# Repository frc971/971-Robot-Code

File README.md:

# **THIS REPO IS NOW ARCHIVED AND READ ONLY.**

# Introduction
This is FRC Team 971's main code repository. There are `README*` files throughout the source tree documenting specifics for their respective folders.

## Contributing
Submissions must be made under the terms of the following Developer Certificate of Origin.

By making a contribution to this project, I certify that:

        (a) The contribution was created in whole or in part by me and I
            have the right to submit it under the open source license
            indicated in the file; or

        (b) The contribution is based upon previous work that, to the best
            of my knowledge, is covered under an appropriate open source
            license and I have the right under that license to submit that
            work with modifications, whether created in whole or in part
            by me, under the same open source license (unless I am
            permitted to submit under a different license), as indicated
            in the file; or

        (c) The contribution was provided directly to me by some other
            person who certified (a), (b) or (c) and I have not modified
            it.

        (d) I understand and agree that this project and the contribution
            are public and that a record of the contribution (including all
            personal information I submit with it, including my sign-off) is
            maintained indefinitely and may be redistributed consistent with
            this project or the open source license(s) involved.

To do this, add the following to your commit message.  Gerrit will enforce that all commits have been signed off.

	Signed-off-by: Random J Developer <random@developer.example.org>

Git has support for adding Signed-off-by lines by using `git commit -s`, or you can setup a git commit hook to automatically sign off your commits.  [Stack Overflow](https://stackoverflow.com/questions/15015894/git-add-signed-off-by-line-using-format-signoff-not-working) has instructions for how to do this if you are interested.

## Table of contents
* [Pathway for new members](#pathway-for-new-members)
    * [Learning C++](#1-learning-c)
        * [XRP](#11-xrp)
    * [Gaining code access](#2-gaining-code-access)
    * [The codelab](#3-the-codelab)
* [Code Reviews](#code-reviews)
    * [Creating SSH Aliases](#creating-ssh-aliases)
* [Codelab](#codelab)
* [Other Information](#other-information)
    * [Roborio Kernel Traces](#roborio-kernel-traces)
    * [Notes on troubleshooting network setup](#notes-on-troubleshooting-network-setup)
    * [LSP Setup for Rust](#lsp-setup-for-rust)
    * [Other resources](#other-resources)

## Pathway for new members

### 1. Learning C++

C++ is what we use to program a majority of the code which runs on the robot.
We generally recommend [this course by codeacademy](https://www.codecademy.com/learn/learn-c-plus-plus) which goes over the basics of C++ as well as OOP.

#### 1.1 XRP

If you are unsure what to work on yet you can start on the [XRP Platform](https://docs.wpilib.org/en/stable/docs/xrp-robot/index.html).
Which basically lets you use smaller robots to learn about robotics through WPILib.

### 2. Gaining code access

You can follow [these steps](./documentation/tutorials/getting-started.md) to access the code.

There is also a document which goes over the basics of using both gerrit and git [here](./documentation/tutorials/git-and-gerrit-basics.md)

### 3. The codelab

Once you have an understanding of C++ and have gone through using all the steps needed to access the code you can start on the codelab, which is a directory living in `frc971/codelab/`. Which goes over a lot of the important introductory information that you need to know to get started when programming the robot.
You can read the [README](./frc971/codelab/README.md), which gives you introduces you to the codelab as well as the concepts you need to understand first.

## Code reviews
We want all code to at least have a second person look it over before it gets merged into the `main` branch. Gerrit has [extensive documentation on starting reviews](https://gerrit-review.googlesource.com/Documentation/user-upload.html).  There is also a good [intro User Guide](https://gerrit-review.googlesource.com/Documentation/intro-user.html) and an [intro to working with Gerrit](https://gerrit-review.googlesource.com/Documentation/intro-gerrit-walkthrough.html) and [Gerrit workflows](https://docs.google.com/presentation/d/1C73UgQdzZDw0gzpaEqIC6SPujZJhqamyqO1XOHjH-uk)

TL;DR: Make and commit your changes, do `git push origin HEAD:refs/for/main`, and then click on the provided link to add reviewers.  If you just upload a change without adding any reviewers, it might sit around for a long time before anybody else notices it.

[git-review](http://manpages.debian.org/cgi-bin/man.cgi?query=git-review) can make the upload process simpler.

To download a commit you can press d or click download on gerrit, then select fetch and paste the command in your terminal. Once you've done that you should switch to a new branch in order to make working on multiple commits easier.
You can do this by doing `git switch -c branch_name`, the branch name can be anything, and will only be public for you, so organize in whatever way you find easy to model.

When programming in C++ we follow [Google's C++ Style Guide](https://google.github.io/styleguide/cppguide.html)

Furthermore, you can run `bazel run //tools/lint:run-ci` to fix linter errors which appear on buildkite.

### Some other useful packages
These aren't strictly necessary to build the code, but Michael found the
additional tools provided by these packages useful to install when working with
the code on May 13, 2018.

> **Note**: These are for local install, most of these tools will be available on the build server

```bash
apt install git
apt install yapf3
apt install python3
apt install bazel
apt install clang-format
```

### Creating ssh aliases

It is also handy to alias logins to the raspberry pi's by adding lines like this to your ~/.ssh/config file:
```console
Host pi-7971-2
    User pi
    ForwardAgent yes
    HostName 10.79.71.102
    StrictHostKeyChecking no
```
or, for the roborio:
```
Host roborio-971
    User admin
    HostName 10.9.71.2
    StrictHostKeyChecking no
```
This allows you to use the alias to `ping`, `ssh`, or run commands like:
```
# Download code to robot #7971's raspberry pi #2
bazel run --config=armv7 -c opt //y2020:download_stripped -- pi-7971-2
```

## Other Information

### Roborio Kernel Traces

Currently (as of 2020.02.26), top tends to produce misleading statistics. As
such, you can get more useful information about CPU usage by using kernel
traces. Sample usage:
```console
# Note that you will need to install the trace-cmd package on the roborio.
# This may be not be a trivial task.
# Start the trace
trace-cmd start -e sched_switch -e workqueue
# Stop the trace
trace-cmd stop
# Save the trace to trace.dat
trace-cmd extract
```
You can then scp the `trace.dat` file to your computer and run `kernelshark
trace.dat` (may require installing the `kernelshark` apt package).

### LSP Setup for Rust

You can run `bazel run //tools:gen_rust_project` to generate a rust-project.json
file which rust-analyzer will pick up. You will need to execute this rule
periodically as it will be outdated whenever the BUILD files change.

> **Note** that there's currently no way to tell rust-analyzer *how* to compile
the code, so while it will give you completion support, go to definition, and
other niceties, it won't show compilation errors or warnings at this point.

### Other resources
  1. Intro to [AOS](./aos/README.md), our robot Operating System
  2. Introductory example: [ping/pong](./aos/events/README.md)
  3. Example of [logging](./aos/events/README.md)

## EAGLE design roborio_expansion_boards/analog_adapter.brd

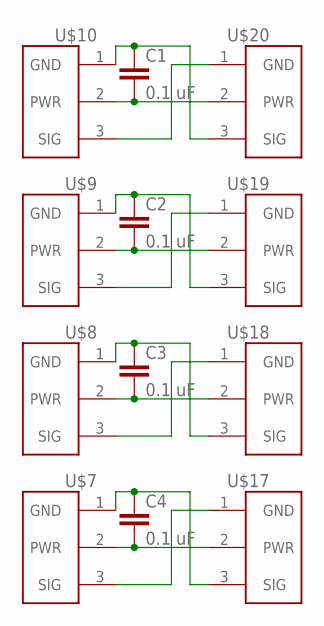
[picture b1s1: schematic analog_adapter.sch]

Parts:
C1, C2, C3, C4: 0.1 uF; 0603
U$7, U$8, U$9, U$10: 22-23-2031GENERIC; PWM_1X3
U$17, U$18, U$19, U$20: 22-23-2031

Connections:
unnamed: C1.1, U$10.1 (GND), U$20.3 (SIG)
unnamed: C1.2, U$10.2 (PWR), U$20.2 (PWR)
unnamed: U$10.3 (SIG), U$20.1 (GND)
unnamed: C2.2, U$9.2 (PWR), U$19.2 (PWR)
unnamed: U$9.3 (SIG), U$19.1 (GND)
unnamed: C3.2, U$8.2 (PWR), U$18.2 (PWR)
unnamed: U$8.3 (SIG), U$18.1 (GND)
unnamed: C4.2, U$7.2 (PWR), U$17.2 (PWR)
unnamed: U$7.3 (SIG), U$17.1 (GND)
unnamed: C4.1, U$7.1 (GND), U$17.3 (SIG)
unnamed: C3.1, U$8.1 (GND), U$18.3 (SIG)
unnamed: C2.1, U$9.1 (GND), U$19.3 (SIG)

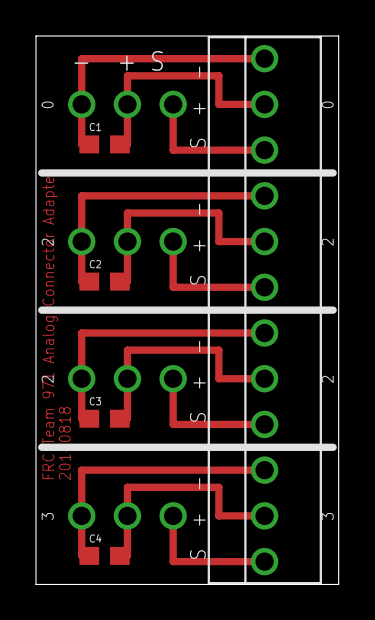
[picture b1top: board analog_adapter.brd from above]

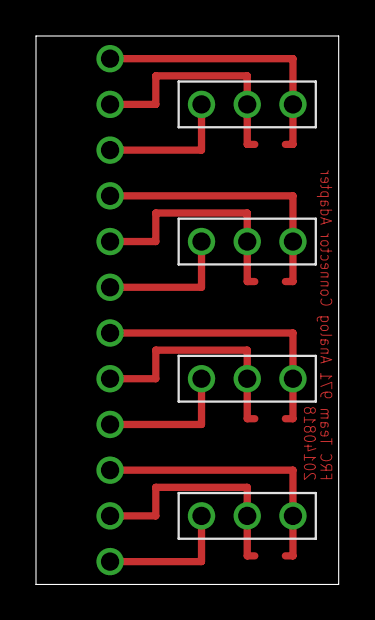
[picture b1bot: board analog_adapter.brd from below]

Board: 2 copper layers, 16.8 x 30.5 mm, 12 parts (4 on the bottom side), 12 nets.

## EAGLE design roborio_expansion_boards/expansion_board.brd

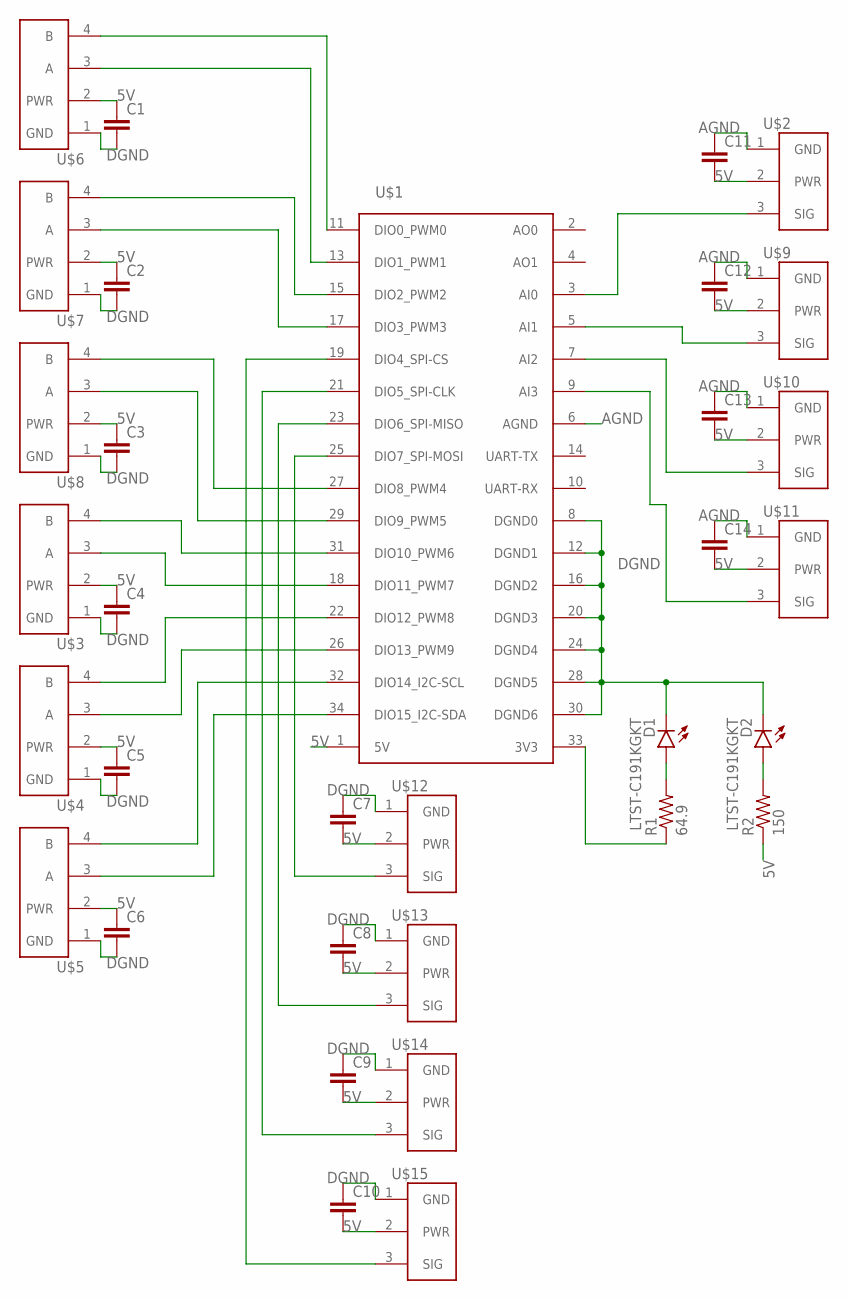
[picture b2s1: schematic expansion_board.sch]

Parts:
C1, C2, C3, C4, C5, C6, C7, C8, C9, C10, C11, C12, C13, C14: CAP0603; 0603
D1, D2: LTST-C191KGKT; LED-0603
R1: 64.9; 0603-RES
R2: 150; 0603-RES
U$1: MXP; SFH11-PBPC-D17-ST-BK
U$2, U$9, U$10, U$11, U$12, U$13, U$14, U$15: 22-23-2031
U$3, U$4, U$5, U$6, U$7, U$8: 22-23-2041

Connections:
5V: C1.1, C2.1, C3.1, C4.1, C5.1, C6.1, C7.2, C8.2, C9.2, C10.2, C11.2, C12.2, C13.2, C14.2, R2.1, U$1.1 (5V), U$2.2 (PWR), U$3.2 (PWR), U$4.2 (PWR), U$5.2 (PWR), U$6.2 (PWR), U$7.2 (PWR), U$8.2 (PWR), U$9.2 (PWR), U$10.2 (PWR), U$11.2 (PWR), U$12.2 (PWR), U$13.2 (PWR), U$14.2 (PWR), U$15.2 (PWR)
AGND: C11.1, C12.1, C13.1, C14.1, U$1.6 (AGND), U$2.1 (GND), U$9.1 (GND), U$10.1 (GND), U$11.1 (GND)
DGND: C1.2, C2.2, C3.2, C4.2, C5.2, C6.2, C7.1, C8.1, C9.1, C10.1, D1.C, D2.C, U$1.8 (DGND0), U$1.12 (DGND1), U$1.16 (DGND2), U$1.20 (DGND3), U$1.24 (DGND4), U$1.28 (DGND5), U$1.30 (DGND6), U$3.1 (GND), U$4.1 (GND), U$5.1 (GND), U$6.1 (GND), U$7.1 (GND), U$8.1 (GND), U$12.1 (GND), U$13.1 (GND), U$14.1 (GND), U$15.1 (GND)
unnamed: U$1.11 (DIO0_PWM0), U$6.4 (B)
unnamed: U$1.13 (DIO1_PWM1), U$6.3 (A)
unnamed: U$1.15 (DIO2_PWM2), U$7.4 (B)
unnamed: U$1.17 (DIO3_PWM3), U$7.3 (A)
unnamed: U$1.27 (DIO8_PWM4), U$8.4 (B)
unnamed: U$1.29 (DIO9_PWM5), U$8.3 (A)
unnamed: U$1.31 (DIO10_PWM6), U$3.4 (B)
unnamed: U$1.18 (DIO11_PWM7), U$3.3 (A)
unnamed: U$1.22 (DIO12_PWM8), U$4.4 (B)
unnamed: U$1.26 (DIO13_PWM9), U$4.3 (A)
unnamed: U$1.32 (DIO14_I2C-SCL), U$5.4 (B)
unnamed: U$1.34 (DIO15_I2C-SDA), U$5.3 (A)
unnamed: U$1.3 (AI0), U$2.3 (SIG)
unnamed: U$1.5 (AI1), U$9.3 (SIG)
unnamed: U$1.7 (AI2), U$10.3 (SIG)
unnamed: U$1.9 (AI3), U$11.3 (SIG)
unnamed: U$1.25 (DIO7_SPI-MOSI), U$12.3 (SIG)
unnamed: U$1.23 (DIO6_SPI-MISO), U$13.3 (SIG)
unnamed: U$1.21 (DIO5_SPI-CLK), U$14.3 (SIG)
unnamed: U$1.19 (DIO4_SPI-CS), U$15.3 (SIG)
unnamed: D1.A, R1.2
unnamed: R1.1, U$1.33 (3V3)
unnamed: D2.A, R2.2

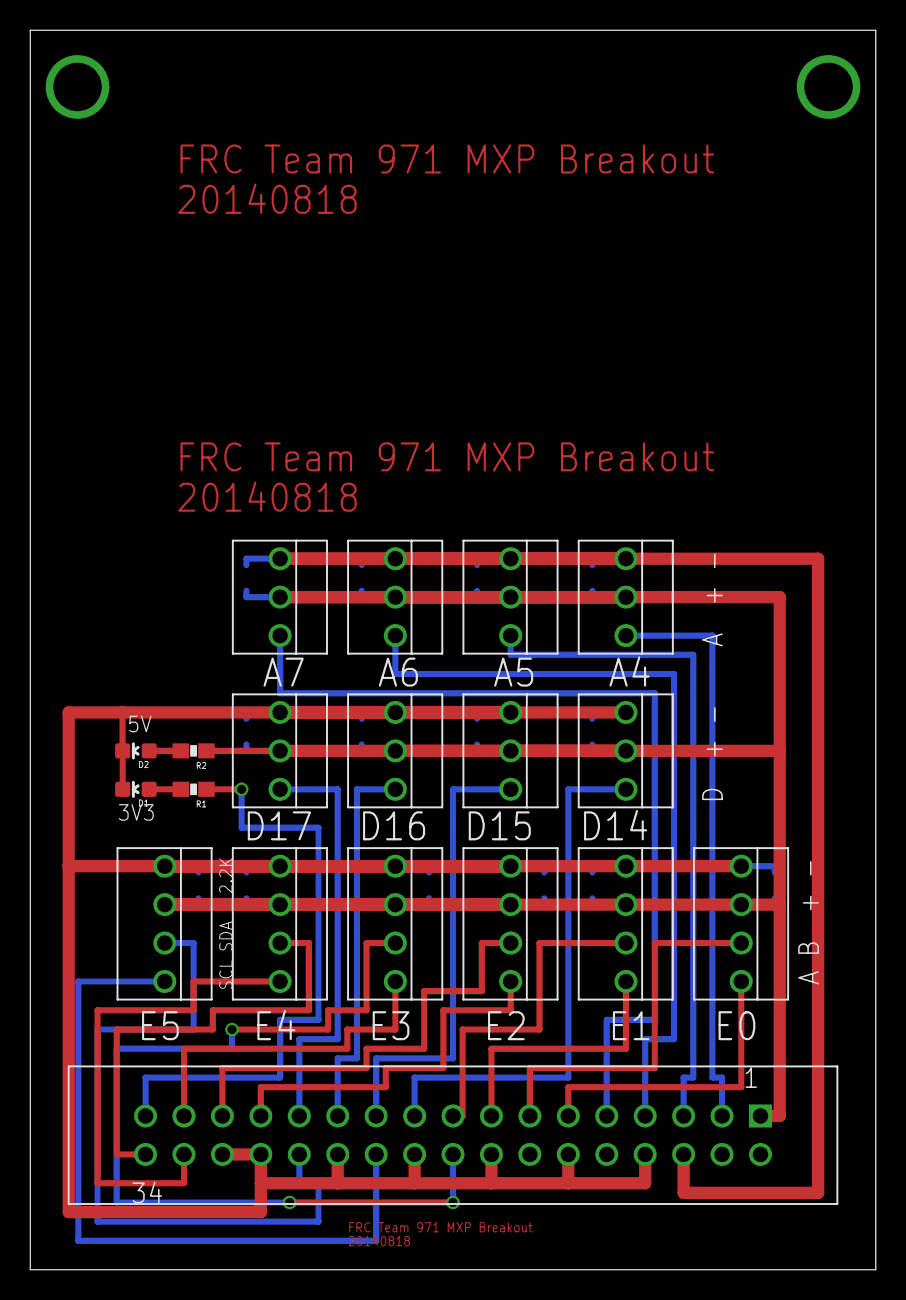
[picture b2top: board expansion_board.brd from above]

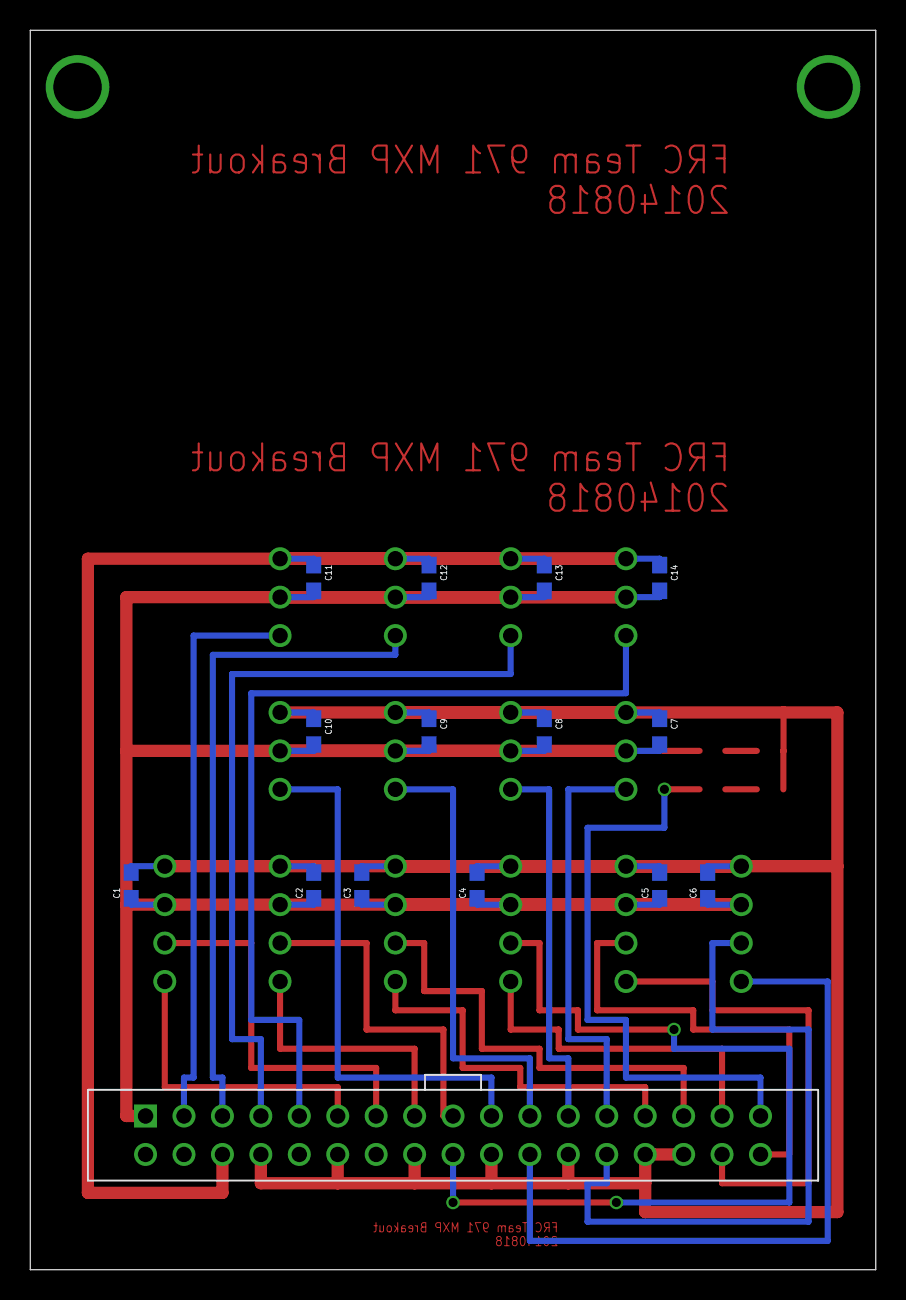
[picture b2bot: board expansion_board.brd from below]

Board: 2 copper layers, 55.9 x 81.9 mm, 33 parts (14 on the bottom side), 26 nets.

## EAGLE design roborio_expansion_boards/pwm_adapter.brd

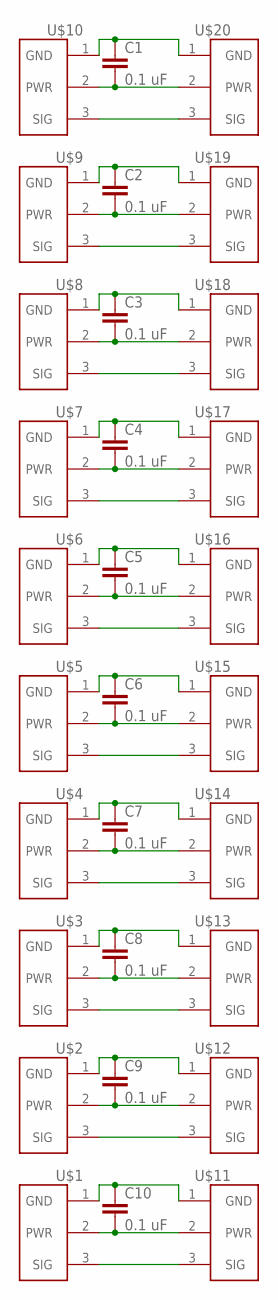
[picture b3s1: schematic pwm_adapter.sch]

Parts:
C1, C2, C3, C4, C5, C6, C7, C8, C9, C10: 0.1 uF; 0603
U$1, U$2, U$3, U$4, U$5, U$6, U$7, U$8, U$9, U$10: 22-23-2031GENERIC; PWM_1X3
U$11, U$12, U$13, U$14, U$15, U$16, U$17, U$18, U$19, U$20: 22-23-2031

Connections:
unnamed: C1.1, U$10.1 (GND), U$20.1 (GND)
unnamed: C1.2, U$10.2 (PWR), U$20.2 (PWR)
unnamed: U$10.3 (SIG), U$20.3 (SIG)
unnamed: C10.1, U$1.1 (GND), U$11.1 (GND)
unnamed: C2.2, U$9.2 (PWR), U$19.2 (PWR)
unnamed: U$9.3 (SIG), U$19.3 (SIG)
unnamed: C9.1, U$2.1 (GND), U$12.1 (GND)
unnamed: C3.2, U$8.2 (PWR), U$18.2 (PWR)
unnamed: U$8.3 (SIG), U$18.3 (SIG)
unnamed: C8.1, U$3.1 (GND), U$13.1 (GND)
unnamed: C4.2, U$7.2 (PWR), U$17.2 (PWR)
unnamed: U$7.3 (SIG), U$17.3 (SIG)
unnamed: C7.1, U$4.1 (GND), U$14.1 (GND)
unnamed: C5.2, U$6.2 (PWR), U$16.2 (PWR)
unnamed: U$6.3 (SIG), U$16.3 (SIG)
unnamed: C6.1, U$5.1 (GND), U$15.1 (GND)
unnamed: C6.2, U$5.2 (PWR), U$15.2 (PWR)
unnamed: U$5.3 (SIG), U$15.3 (SIG)
unnamed: C5.1, U$6.1 (GND), U$16.1 (GND)
unnamed: C7.2, U$4.2 (PWR), U$14.2 (PWR)
unnamed: U$4.3 (SIG), U$14.3 (SIG)
unnamed: C4.1, U$7.1 (GND), U$17.1 (GND)
unnamed: C8.2, U$3.2 (PWR), U$13.2 (PWR)
unnamed: U$3.3 (SIG), U$13.3 (SIG)
unnamed: C3.1, U$8.1 (GND), U$18.1 (GND)
unnamed: C9.2, U$2.2 (PWR), U$12.2 (PWR)
unnamed: U$2.3 (SIG), U$12.3 (SIG)
unnamed: C2.1, U$9.1 (GND), U$19.1 (GND)
unnamed: C10.2, U$1.2 (PWR), U$11.2 (PWR)
unnamed: U$1.3 (SIG), U$11.3 (SIG)

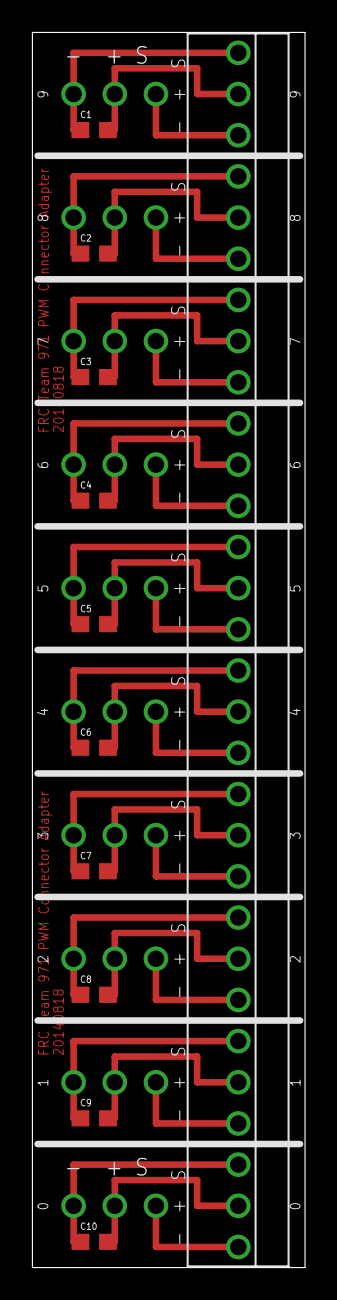
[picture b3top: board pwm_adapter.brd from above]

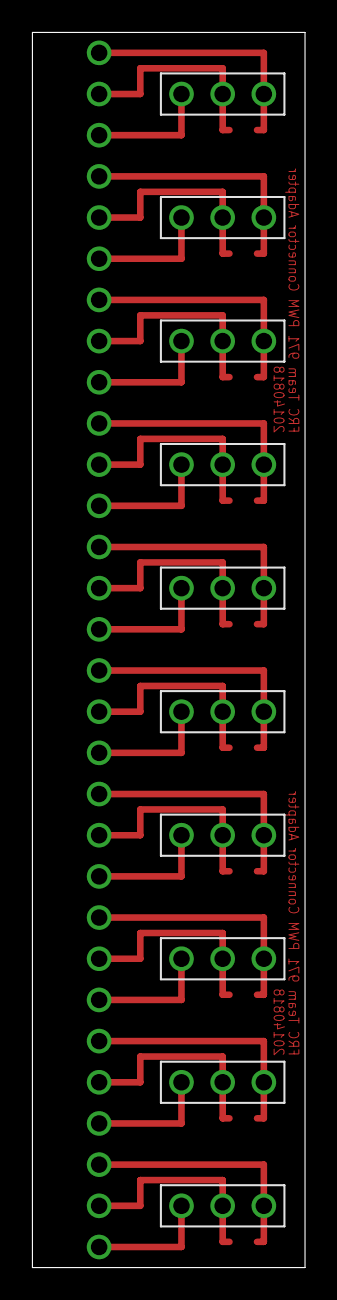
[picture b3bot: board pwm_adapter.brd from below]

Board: 2 copper layers, 16.8 x 76.2 mm, 30 parts (10 on the bottom side), 30 nets.

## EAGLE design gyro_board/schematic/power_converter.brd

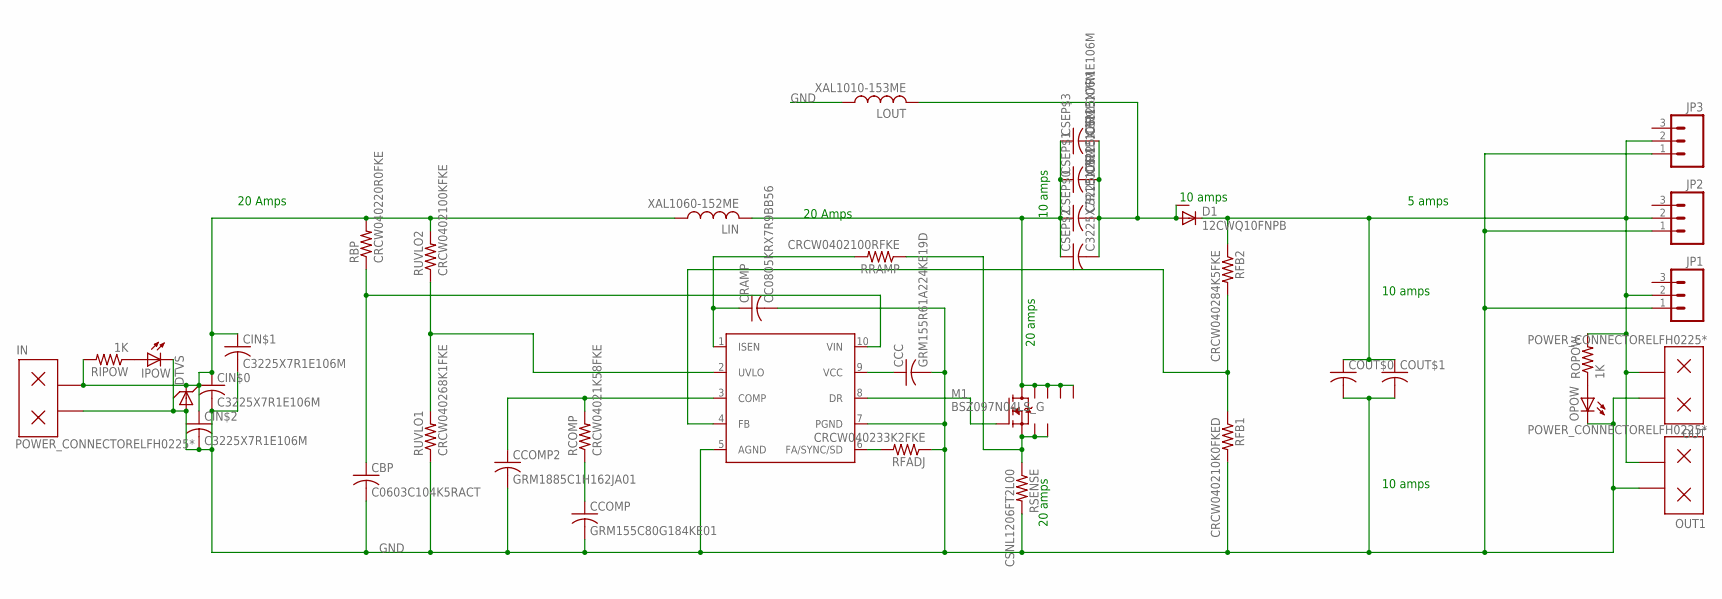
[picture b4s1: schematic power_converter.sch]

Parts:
CBP: C0603C104K5RACT; C0603
CCC: GRM155R61A224KE19D; C0402
CCOMP: GRM155C80G184KE01; C0402
CCOMP2: GRM1885C1H162JA01; C0603
CIN$0, CIN$1, CIN$2: C3225X7R1E106M; C1210
COUT$0, COUT$1: C-USRR71C331MDN1; RR71C331MDN1
CRAMP: CC0805KRX7R9BB56; C0805
CSEP$0, CSEP$1, CSEP$2, CSEP$3: C3225X7R1E106M; C1210
D1: 12CWQ10FNPB; D-PAK
DTVS: MMSZ5246BT1G; SOD-123
IN: POWER_CONNECTORELFH0225*; ELFH0225*
IPOW: LEDCHIPLED_0805; CHIPLED_0805
JP1, JP2, JP3: M03PTH; 1X03
LIN: XAL1060-152ME; 1060-152
LOUT: XAL1010-153ME; 1010-153
M1: BSZ097N04LS_G; PG-TSDSON8
OPOW: LEDCHIPLED_0805; CHIPLED_0805
OUT, OUT1: POWER_CONNECTORELFH0225*; ELFH0225*
RBP: CRCW040220R0FKE; R0402
RCOMP: CRCW04021K58FKE; R0402
RFADJ: CRCW040233K2FKE; R0402
RFB1: CRCW040210K0FKED; R0402
RFB2: CRCW040284K5FKE; R0402
RIPOW: 1K; R1206
ROPOW: 1K; R1206
RRAMP: CRCW0402100RFKE; R0402
RSENSE: CSNL1206FT2L00; M1206
RUVLO1: CRCW040268K1FKE; R0402
RUVLO2: CRCW0402100KFKE; R0402
U$1: LM3481; MSOP10

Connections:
GND: CBP.2, CCC.2, CCOMP.2, CCOMP2.2, CIN$0.2, CIN$1.2, CIN$2.2, COUT$0.- (2), COUT$1.- (2), CRAMP.2, DTVS.ANODE (A), IN.P$1, IPOW.C, JP1.1, JP2.1, JP3.1, LOUT.P$1 (1), OPOW.C, OUT.P$2, OUT1.P$2, RFADJ.1, RFB1.2, RSENSE.2, RUVLO1.1, U$1.5 (AGND), U$1.7 (PGND)
unnamed: CBP.1, RBP.1, U$1.10 (VIN)
unnamed: CIN$0.1, CIN$1.1, CIN$2.1, DTVS.CATHODE (C), IN.P$2, LIN.P$1 (1), RBP.2, RIPOW.2, RUVLO2.2
unnamed: CCC.1, U$1.9 (VCC)
unnamed: RUVLO1.2, RUVLO2.1, U$1.2 (UVLO)
unnamed: CCOMP2.1, RCOMP.2, U$1.3 (COMP)
unnamed: CCOMP.1, RCOMP.1
unnamed: CRAMP.1, RRAMP.2, U$1.1 (ISEN)
unnamed: RFADJ.2, U$1.6 (FA/SYNC/SD)
unnamed: M1.S$0 (S), M1.S$1, M1.S$2, RRAMP.1, RSENSE.1
unnamed: M1.G, U$1.8 (DR)
unnamed: CSEP$0.2, CSEP$1.2, CSEP$2.2, CSEP$3.2, D1.ANODE$0 (A), D1.ANODE$1 (A1), LOUT.P$2 (2)
unnamed: CSEP$0.1, CSEP$1.1, CSEP$2.1, CSEP$3.1, LIN.P$2 (2), M1.D$0 (D), M1.D$1, M1.D$2, M1.D$3, M1.D$4
unnamed: COUT$0.+ (1), COUT$1.+ (1), D1.CATHODE (C), JP1.2, JP2.2, JP3.2, OUT.P$1, OUT1.P$1, RFB2.1, ROPOW.2
unnamed: RFB1.1, RFB2.2, U$1.4 (FB)
unnamed: IPOW.A, RIPOW.1
unnamed: OPOW.A, ROPOW.1

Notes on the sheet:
20 Amps
10 amps
20 amps
5 amps

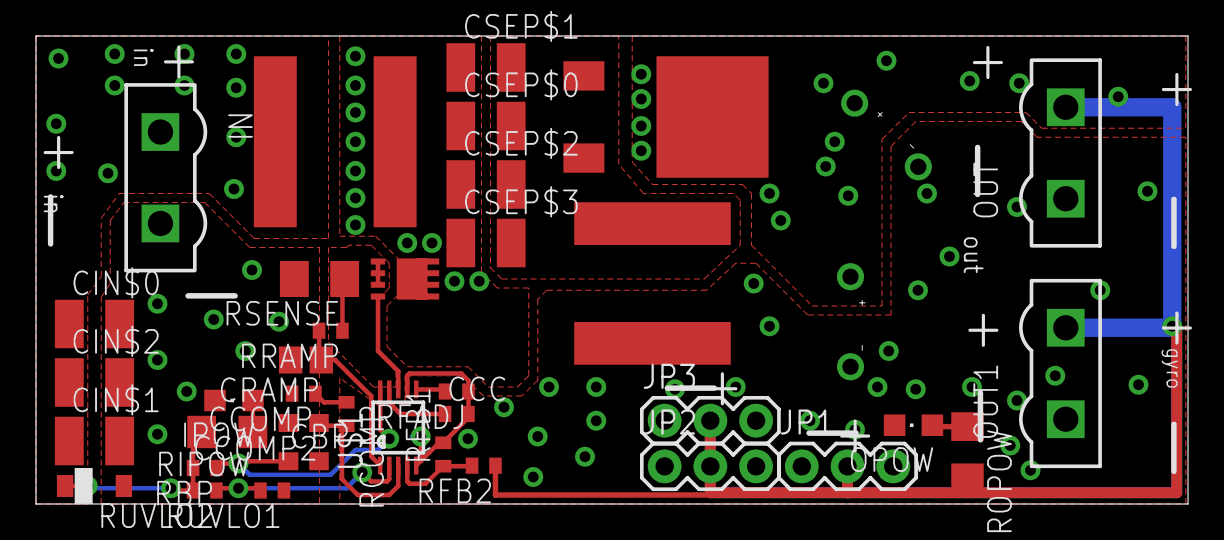
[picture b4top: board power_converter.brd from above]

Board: 2 copper layers, 64.0 x 26.0 mm, 39 parts (0 on the bottom side), 17 nets.

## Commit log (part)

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2024-09-23 Scouting app: fix action submission
    In the Review screen, ending the teleop phase showed up as "9" since it was not caught in the switch case in entry.ng.html. Additionally, if
    the scout switched between the endgame and review screen multiple times,
    there would be multiple penalty actions since the penalty action created
    when they went to the review page would not be deleted when they go back
    to the endgame screen. This patch addresses these problems.
2024-10-05 Add an experience buffer and tests.
    This sets us up to shard across the actor dimension and randomly sample
    actions.
2024-10-12 Set up control loops for y2024_swerve testing
2024-10-17 Fix nullptr dereference in dlqr()
2024-10-17 Cloning the repo tutorial changes
    I ran into a problem when I was following the tutorial to duplicate the repo.
    We tried to make the tutorial more specific on how to clone the repo
    and use the instructions on gerrit.
2024-10-19 Split Soft Actor-Criticl problem out into a class
    This sets us up to optimize multiple, different things.
2024-10-20 Add error message for no schema in aos/logging/config_remapper.cc
2024-10-26 Fix goal not being passed to gradient from data
2024-10-27 Put step number on top of LQR plots
    Makes it easier to tell when they update.
2024-10-27 Reorganize batched training functions in train.py
    By interleaving them with the actual logic, they were making it harder
    to see the logic.
2024-10-27 Quiet down printing while training
    All the debugging makes it hard to see what is happening.
2024-10-27 Add flag to scale target entropy.
    This helps change how much exploration to do compared to how much to do
    the optimal action. Less entropy, ie a larger scalar, means that we
    will explore less. This helps swerve not get stuck at the limits.
2024-10-27 Add flag to set initial alpha for SAC
    This makes it so we can start with the correct entropy relatively
    easily without having to do lots of gradient decent steps.
2024-10-27 Add papers we used to the code
2024-10-30 Update CTRE libraries to phoenix 6 alpha-2
2024-10-30 Add JoystickGoal option to swerve Goal message
2024-11-01 Template jacobian.h on Scalar type
    This makes it so that we can run numerical Jacobian calculations on
    single-precision floats when we want to.
2024-11-02 Switch to BGR input in threshold.cc
2024-11-02 Clean up timing labels
2024-11-02 More todo comments for potential optimizations
2024-11-05 Make threshold code templated on image format
    Remove it from the top level gpu detector. This simplifies the code a
    lot by removing a bunch of unneeded template code from the main detector
    class.
2024-11-09 cleanup
2024-11-18 Remove start_binary from robot_downloader
    Since ~2019, we haven't used the start_list.txt generated from start_binary. The processes are instead written in the aos_config. The removal is nice to avoid confusion.
2024-11-28 move codelab into subfolder
    We'd like to add more codelabs.
2024-11-30 Add generic EKF class
2024-12-01 Mark sandbox-breaking calibration test "manual"
    This test went outside of the bazel sandbox to try to locate files on
    the local filesystem; mark it manual to prevent it being run by default
    until we can move the log dependency into a proper dependendency.
    Also, make it so that we actually print out stdout/stderr from the
    process that was failing to make error messages clearer.
2024-12-06 Adding visualization tool for collected points during intrinsics Draw charuco points on the image
    Also, fixed issue with using hard-coded 640x480 image size
    Added ability to flip image (true by default) to make it more intuitive
    Bump reprojection error tolerance to 5.0, so we can at least save the intrinsics,
    but warn if error is > 2.0
    Add captions to show how many images are captured and whether pose estimate is valid
    Allow saving of images to folder, for later loading and processing.
2024-12-09 Fix copy-paste error
2024-12-12 Blind change to maybe transparently deal with endian issues for 16 bit images
2024-12-15 Add velocity dynamics-based EKF
    This provides a more principled estimator that can be used with the
    linear swerve controller.
    This does not directly provide estimation of X/Y states.
2024-12-19 Assorted cleanup in prep for pull request
2024-12-28 Create a linear velocity controller for swerve specifically
    This puts together some of the pieces created in prior commits to
    provide a simplistic LQR-based controller for controlling the velocity
    of a swerve drivebase.
2024-12-28 Add the yocto sysroot for arm64
2025-01-06 Add drivetrain priority setting to bot3
2025-01-06 Created a y2025 folder and copied boilerplate code
2025-01-07 add swerve to joystick
2025-01-12 Fixed documentation bug where user was directed to create ~/.ssh/aliases instead of ~/.ssh/config.
2025-01-12 Add elevator constants
    Constants added:
    * elevator set point constants
    * elevator PotAndAbsEncoderConstants (zeroing_constants and potentiometer_offset)
    * elevator encoder and pot ratios in constants.h
2025-01-13 Add elevator to wpilib_interface
    There are two elevator krakens so I named them elevator_one and elevator_two
2025-01-15 Add pivot WPILib interface
2025-01-15 Create ui for autonomous path planning
2025-01-15 Add pivot superstructure Add pivot superstructure test
2025-01-16 Add End Effector superstructure
2025-01-19 Lower apriltag pixel border
    I'm doing this now that we're using the 8 parameter model. The reason
    why this pixel border was so large before is because we couldn't trust
    the detections we get on the edge of the image. But now that we can
    detect them better we should be okay to turn this down.
2025-01-20 Create autonomous controller
2025-01-20 Add preliminary buttons to control superstructure
2025-01-21 Add swerve to y2024_bot3
2025-01-23 Add accel_weight to y2024_bot3
    Didn't get caught in buildkite, causing main to fail
2025-01-24 Update 2025 configs
2025-01-25 Add climber constants and flatbuffers
2025-01-25 Add climber superstructure
2025-01-25 Add auto_align to swerve controller
2025-01-25 Add new robot constants
2025-01-26 Update Driver Ranking and View Tabs
2025-01-28 Add y2025 swerve replay
2025-02-01 Add end_effector wpilib
2025-02-01 Add notes to webserver
2025-02-05 Add schema checker to AOS config
    The aos_config flattener did not check we had a schema for each channel
    so when on the robot, things like aos_dump crash. This is a very easy
    thing to miss especially for new people(like I did) and the segfault
    is very cryptic so this should help with that. Also, fix broken ones.
2025-02-06 Fix --config=roborio
2025-02-08 Create visualizer for AprilTag locations
2025-02-08 Add 2025 localizer
    The goal of this is to give us robust localization on the field this
    year, but because we haven't done full localization with swerve yet
    we're implementing it using wpilib, weighted averaging, and a kalman
    filter. More is explained in the comment in localizer.h
    This also removes the x, y, and theta estimation in naive_estimator. It
    no longer outputs x and y and the theta it uses for correction in the
2025-02-08 Correct wrist constants
2025-02-09 Add auto align
2025-02-09 Make auto align latch
2025-02-09 implement auto align into swerve_control_loops.cc
2025-02-10 Update wpilib_interface for wrist
2025-02-10 Update constants and add more goals and update joysticks
2025-02-11 Tune auto align PID parameters
    Changes from 02.10 drive practice
2025-02-11 Add climbing
    This adds proper joystick goals for climbing and makes it current
    controlled.
2025-02-12 Slow down omega
2025-02-12 Add Notes and View Tabs
2025-02-13 Update constants
2025-02-15 Update constants for elevator and joystick_reader
2025-02-15 Update autonomous_controller to use the localizer
    This also makes some other minor changes like tuning the position gain
    on the PID and adding a test spline we used for making sure this worked
    during 02/13 drive practice.
2025-02-15 Add algae goals
2025-02-16 Add camera focus binary
    The idea of this binary is to load it on the orin but only as a utility
    to help focus the cameras. So, it's not going to be running be default.
    A higher number is a "more" focused camera, sent via LOG(INFO).
2025-02-17 Make robot choose front/back scoring based on localization
2025-02-17 Add infrastructure for 2025 autonomous actions
2025-02-17 Update auto align to be a bit slower
    This also makes it work with the software bot, which currently does not
    care about left and right yet.
2025-02-18 Make HP_locations snake case
2025-02-18 Negate x and y when on red alliance
2025-02-20 Add a more stable option for the ekf
2025-02-22 Update eigen to version 3.4.90
    Ran `./doc/allwpilib_subtree.sh add third_party/eigen_test https://gitlab.com/libeigen/eigen master`
    Fixes due to updating
    * Updated third_party/eigen/BUILD to have headers from `Eigen/src/plugins/**`
    * Suppressed deprecated warnings in //y2017/vision:target_finder
    * Removed unused variable in y2024/localizer/localizer.h
    * Removed unused variable in y2023/localizer/localizer.h
2025-02-22 Re order calibration and intrinsics to match robot
    The cameras swapped sides, this commit updates the camera ids and
    intrinsics to match that.
2025-02-22 Data Entry fixes
    Fix undo after scored coral, add dropped to pick up.
    Fix l1-l4 design.
2025-02-23 Do better error handling in led indicator
2025-02-23 Fix an unneeded LOG(INFO)
2025-02-25 Add auto align d loop and theta lock, and update localization
2025-02-25 Update joysticks for new swerve controller
2025-02-25 Fix Entry Undo and Revive
2025-02-25 Separate steer and drive current
2025-02-25 Add closest theta auto align
2025-02-26 Small fixes from 02.25
2025-02-27 Add velocity error to autonomous controller
2025-02-27 Fix actions breaking when a new section is added
2025-02-28 Let spit l1 voltage be different from spit voltage
2025-03-01 Pivot/Elevator moves first
    Add collision avoidance with reef
2025-03-01 Add flip to autonomous webui and add more autos
2025-03-02 Add climb set point for elevator, pivot, and wrist
2025-03-02 Add Frame Logger
    This is a binary on the orins which allows you to log frames captured
    from the camera at regular intervals specified as dt in the file.
2025-03-03 Add Barge and Processor Auto Orient
2025-03-04 Tune up subsystems
2025-03-04 Hardcode 20s to run for autos
2025-03-04 Add algae ground buttons and goal
2025-03-05 Make naive estimator use autonomous init
2025-03-06 Update View Tab
2025-03-09 Reset Penalties
2025-03-15 Add deadband to controller
2025-03-15 Add user button to swerve control loops
2025-03-15 Small button changes
2025-03-15 Zero Wrist
2025-03-19 change elevator zero
2025-03-21 Add Elevator and Pivot IK
2025-03-26 Actually correct mass and moi
2025-03-27 Use Can Ranges in y2025
2025-04-01 Use correct noise in kalman filter localizer
2025-04-01 Auto align reef collision avoidance
    Goes to a pose offset from the final goal pose first, then goes to
    final pose.
2025-04-10 Make Entry+Ranking Navigation Easier

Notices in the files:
parts and their libraries:
SparkFun-Connectors: Licensing: CC v3.0 Share-Alike You are welcome to use this library for commercial purposes.
SparkFun-LED: Licensing: Creative Commons ShareAlike 4.0 International - https://creativecommons.org/licenses/by-sa/4.0
